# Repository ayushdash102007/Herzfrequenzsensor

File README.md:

# Herzfrequenzsensor

Entwicklung einer eigenen Leiterplatte (PCB) zur Messung der Herzfrequenz mit einem optischen Herzfrequenzsensor. Die Schaltung umfasst eine Spannungsregelung sowie eine I²C-Schnittstelle zur Kommunikation mit einem Mikrocontroller.

**Status:** [z. B. Entworfen, Gerber-Dateien erstellt]

## Komponenten

| Bauteil | Funktion |
|---|---|
| ESP32-S3-WROOM-1 | Mikrocontroller |
| AMS1117 | Spannungsregler (5 V → 3,3 V) |
| AP2112K-1.8 | Spannungsregler (3,3 V → 1,8 V) |
| MAX30102 | Optischer Herzfrequenzsensor (I²C) |
| USB-C-Buchse | Stromversorgung und Programmierung |

## Schaltplan

## Leiterplatte (PCB)

## 3D-Ansicht

## Was ich gelernt habe
1. Entwurf eines Schaltplans und PCB-Layouts mit KiCad
2. Lesen von Datenblättern und Auswahl passender Bauteile
3. Auslegung der Spannungsversorgung (5 V → 3,3 V → 1,8 V)
4. Entwurf einer Platine mit ESP32-S3 und I²C-Sensor
5. Prüfung mit Electrical Rules Check (ERC) und Design Rules Check (DRC)
6. Erzeugen von Gerber-Dateien für die Fertigung

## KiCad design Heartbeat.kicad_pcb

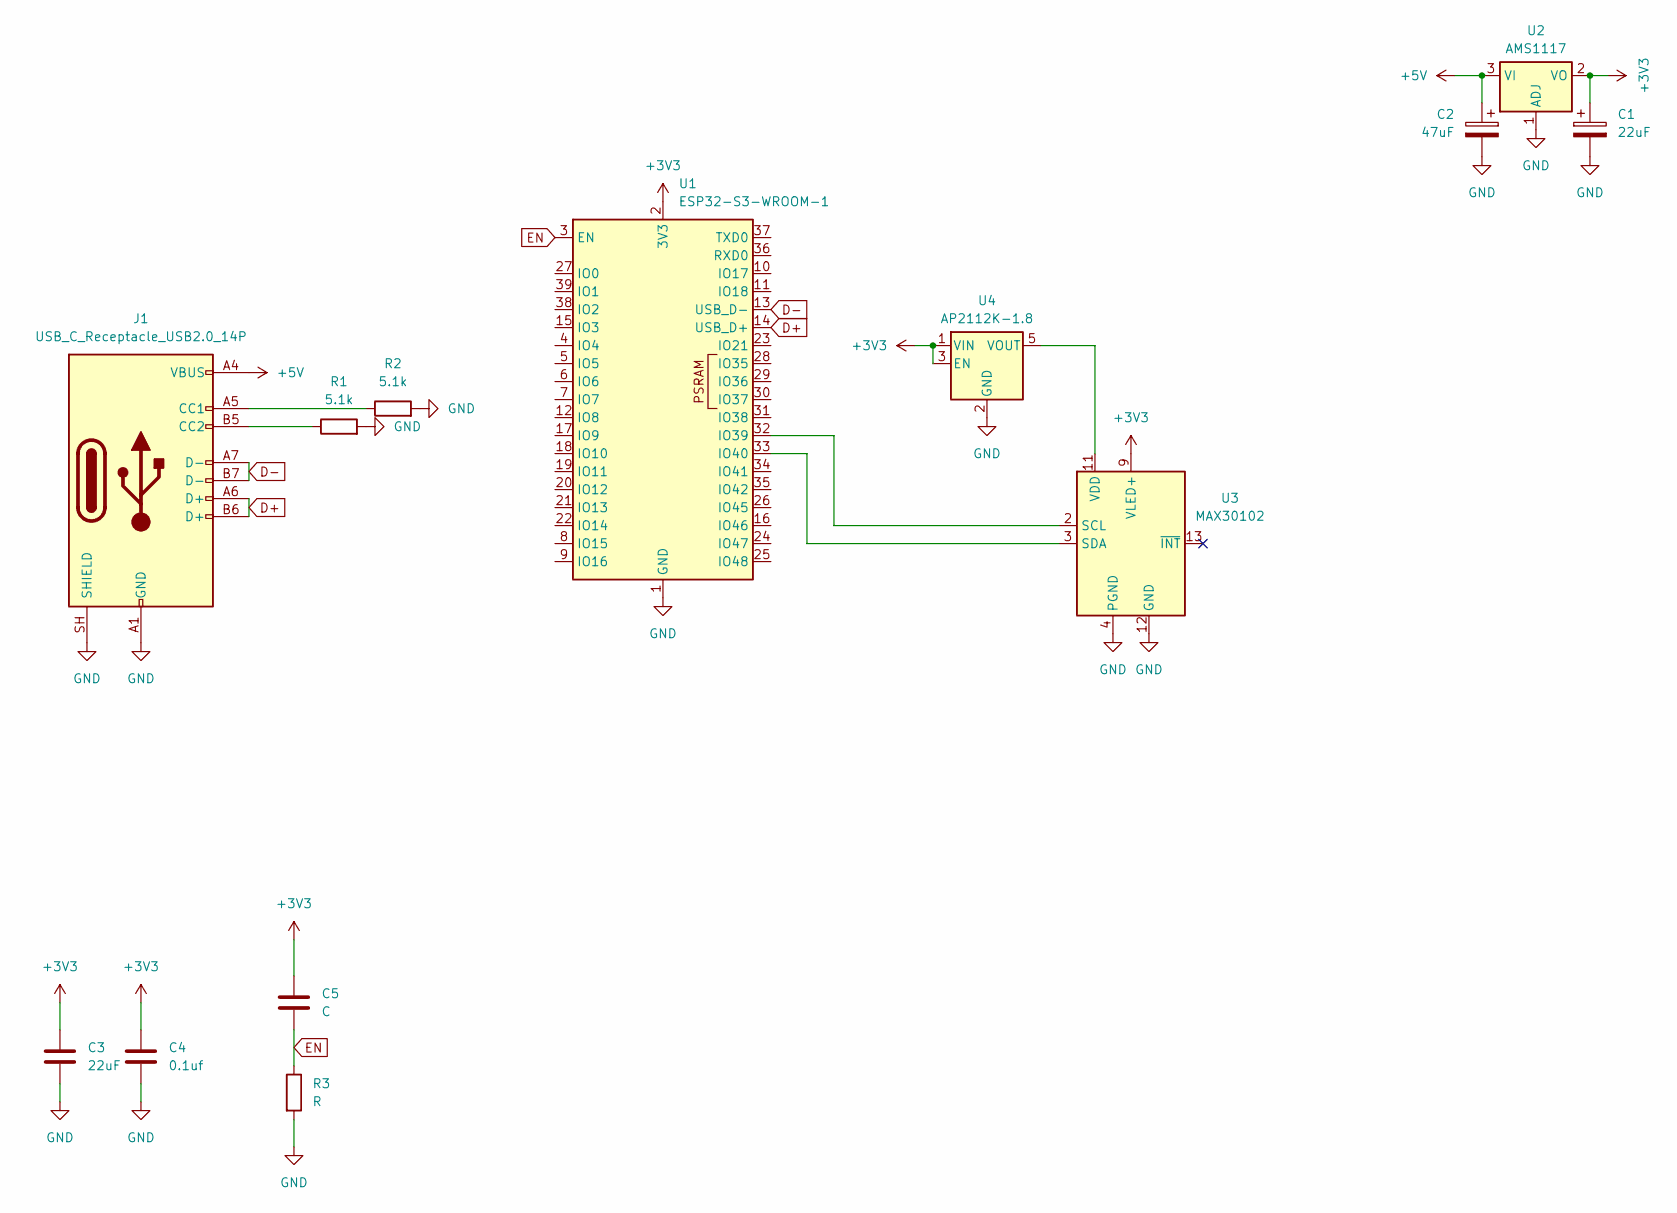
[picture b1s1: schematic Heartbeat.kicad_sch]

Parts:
C1, C3: 22uF; C_0402_1005Metric
C2: 47uF; C_0402_1005Metric
C4: 0.1uf; C_0402_1005Metric
C5: C; C_0402_1005Metric
J1: USB_C_Receptacle_USB2.0_14P; USB_C_Receptacle_GCT_USB4105-xx-A_16P_TopMnt_Horizontal
R1, R2: 5.1k; R_0402_1005Metric
R3: R; R_0402_1005Metric
U1: ESP32-S3-WROOM-1
U2: AMS1117; SOT-223-3_TabPin2
U3: MAX30102; Maxim_OLGA-14_3.3x5.6mm_P0.8mm
U4: AP2112K-1.8; SOT-23-5

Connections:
+3V3: C1.1, C3.1, C4.1, C5.1, U1.2 (3V3), U2.2 (VO), U3.9 (VLED+), U3.10 (VLED+), U4.1 (VIN), U4.3 (EN)
+5V: C2.1, J1.A4 (VBUS), J1.A9 (VBUS), J1.B4 (VBUS), J1.B9 (VBUS), U2.3 (VI)
D+: J1.A6 (D+), J1.B6 (D+), U1.14 (USB_D+)
D-: J1.A7 (D-), J1.B7 (D-), U1.13 (USB_D-)
EN: C5.2, R3.1, U1.3 (EN)
GND: C1.2, C2.2, C3.2, C4.2, J1.A1 (GND), J1.A12 (GND), J1.B1 (GND), J1.B12 (GND), J1.SH (SHIELD), R1.2, R2.2, R3.2, U1.1 (GND), U1.40 (GND), U1.41 (GND), U2.1 (ADJ), U3.4 (PGND), U3.12 (GND), U4.2 (GND)
unnamed: J1.A5 (CC1), R2.1
unnamed: J1.B5 (CC2), R1.1
unnamed: U1.32 (IO39), U3.2 (SCL)
unnamed: U1.33 (IO40), U3.3 (SDA)
unnamed: U3.11 (VDD), U4.5 (VOUT)

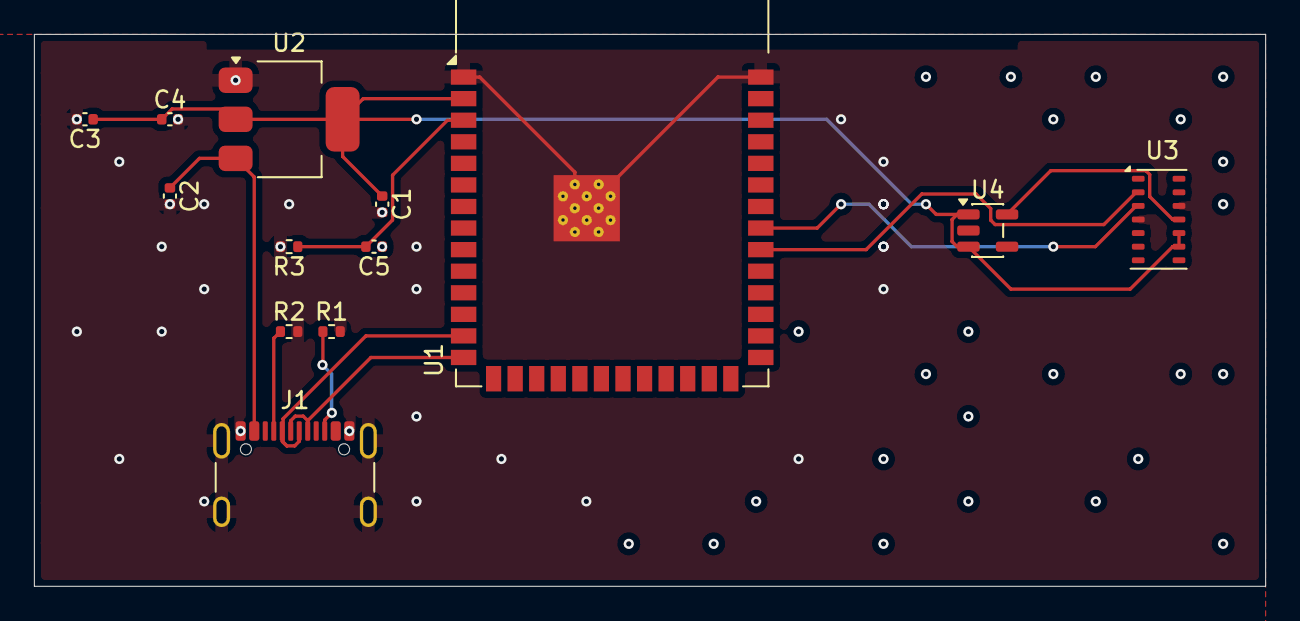
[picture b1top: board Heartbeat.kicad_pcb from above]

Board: 2 copper layers, 72.5 x 32.5 mm, 13 parts (0 on the bottom side), 11 nets.
